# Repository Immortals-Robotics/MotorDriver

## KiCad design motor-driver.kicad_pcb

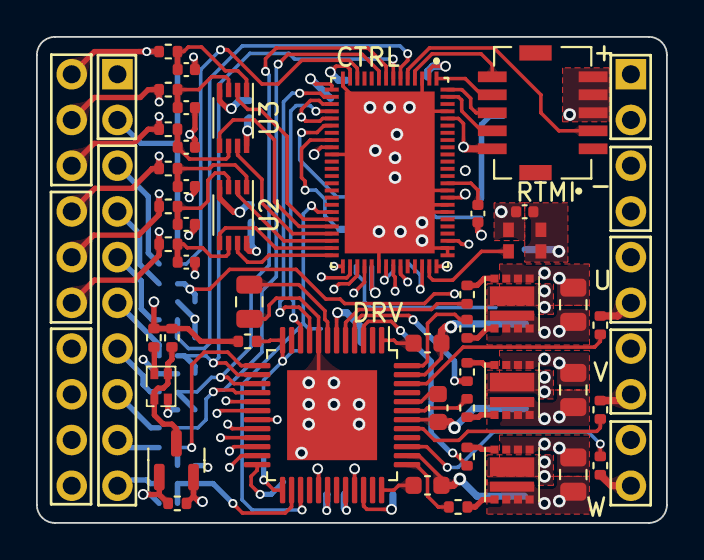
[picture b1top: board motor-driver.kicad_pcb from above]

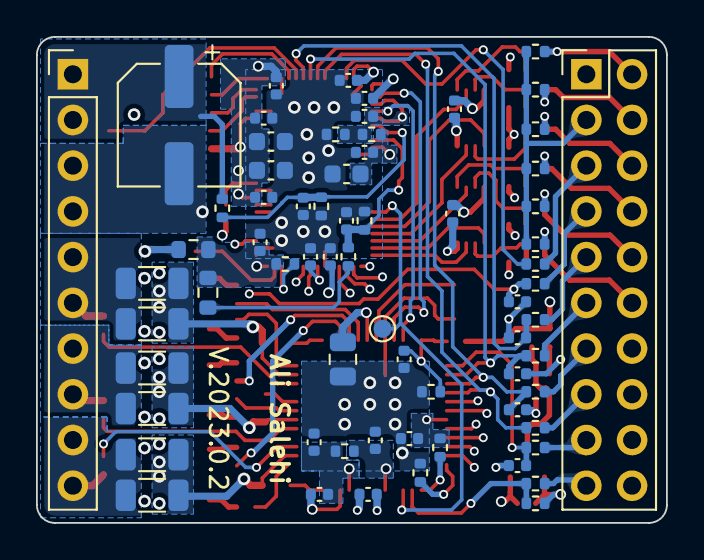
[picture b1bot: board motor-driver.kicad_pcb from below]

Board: 4 copper layers, 35.0 x 27.0 mm, 112 parts (67 on the bottom side), 98 nets.

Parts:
C1, C2, C3: 1nF; C_0402_1005Metric
C4, C5, C6, C41, C42, C43, C44, C45: 100pF; C_0402_1005Metric
C7, C8, C11, C12, C13, C14, C15, C16, C18, C19, C20, C21, C22, C23, C27, C28, C32, C33, C35, C36, C40: 100nF; C_0402_1005Metric
C9, C17: 4.7uF; C_0603_1608Metric
C10, C29, C30, C31: 470nF; C_0603_1608Metric
C24, C25, C37, C38, C39: 2.2uF; C_0805_2012Metric
C26: 22nF; C_0402_1005Metric
C34: 47uF; CP_Elec_6.3x7.7
D1: B2972USNB05
FB1: 600R, 1A; R_0603_1608Metric
J2: SIGNAL; PinHeader_2x10_P2.54mm_Vertical
J3: PWR; PinHeader_1x10_P2.54mm_Vertical
J4: RTMI; HRS_DF20EF-10DP-1V(52)
Q1: BSS138; SOT-23
Q4, Q5, Q6: SIZ342ADT; SIZ340DTT1GE3
R1, R2, R3, R4, R5, R6, R10, R11, R12, R15, R16, R20, R21, R22, R23: 4.7K; R_0402_1005Metric
R7, R8, R9, R19: 1K; R_0402_1005Metric
R13, R50: 10K; R_0402_1005Metric
R14, R17: 0; R_0402_1005Metric
R18: 47K; R_0402_1005Metric
R24, R27, R28, R29, R45: 270; R_0402_1005Metric
R25, R26, R46: 150; R_0402_1005Metric
R30, R31, R32, R33, R34, R35, R42, R43, R44: 10; R_0402_1005Metric
R36, R37, R38, R39, R40, R41: 0.005, 1W; R_1206_3216Metric
R47, R48: 330; R_0402_1005Metric
R49: 100; R_0402_1005Metric
R51: 1; R_0402_1005Metric
TH1: 10K; R_0603_1608Metric
TP1: EN TestPoint; TestPoint_Pad_D1.0mm
U1: TMC4671; QFN40P650X1050X90-77N
U2, U3: 74LVC3G17; VSSOP-8_2.3x2mm_P0.5mm
U4: TMC6200; TQFP-48-1EP_7x7mm_P0.5mm_EP5x5mm
XTAL1: MC2016, 25MHz; XTAL_MC2016K25_2X1P6_AVX

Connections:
+2V5: C36.2, R20.1, R21.2, U1.17 (ADC_I0_NEG), U1.19 (ADC_I1_NEG)
+3.3V: C7.2, C8.2, C9.2, C10.2, C11.2, C12.2, C13.2, C14.2, C15.2, C16.2, C33.2, FB1.1, J2.1, J4.1, R13.2, R17.1, TH1.1, U1.2 (VCCIO1), U1.13 (VCCIO2), U1.43 (VCCIO3), U1.52 (VCCIO4), U1.61 (VCCIO5), U1.72 (VCCIO6), U2.8 (VCC), U3.8 (VCC), U4.19 (VCC_IO)
+5V: C17.2, C18.2, J2.3, R4.2, R5.2, R6.2, R10.2, R11.2, R12.2, R15.2, R20.2, R47.2, R48.2, U1.23 (V5)
+24V: C23.2, C34.1, C37.2, C38.2, C39.2, J3.1, J3.2, Q4.2, Q4.3, Q4.4, Q4.10, Q5.2, Q5.3, Q5.4, Q5.10, Q6.2, Q6.3, Q6.4, Q6.10, R18.2, R51.1, U4.29 (VSA)
/CTRL_EN: C41.2, R24.1, U1.55 (ENI)
/CTRL_STATUS: R25.1, U1.12 (STATUS)
/CUR_U: U1.16 (ADC_I0_POS), U4.9 (CURU)
/CUR_V: U1.18 (ADC_I1_POS), U4.10 (CURV)
/Controller/ADC_VM: C35.2, R18.1, R19.2, U1.20 (ADC_VM)
/Controller/DRV_EN: TP1.1, U1.32 (ENO), U4.27 (DRV_EN)
/Controller/UH: U1.39 (PWM_UX1_H), U4.17 (UH)
/Controller/UL: U1.40 (PWM_UX1_L), U4.18 (UL)
/Controller/VH: U1.41 (PWM_VX2_H), U4.20 (VH)
/Controller/VL: U1.42 (PWM_VX2_L), U4.21 (VL)
/Controller/WH: U1.46 (PWM_WY1_H), U4.22 (WH)
/Controller/WL: U1.47 (PWM_WY1_L), U4.23 (WL)
/DBG_SPI_MISO: J4.9, U1.4 (GPIO6/AENC_VN_MCD/DBGSPI_MISO)
/DBG_SPI_MOSI: J4.7, U1.1 (GPIO5/AENC_UX_MCD/DBGSPI_MOSI)
/DBG_SPI_SCK: J4.5, U1.76 (GPIO4/AGPI_B_MCD/DBGSPI_SCK)
/DBG_SPI_TRG: J4.4, U1.5 (GPIO7/AENC_WY_MCD/DBGSPI_TRG)
/DRV_FAULT: R26.1, R49.2, U4.26 (FAULT)
/Driver/HSU: R30.1, U4.48 (HSU)
/Driver/HSV: R32.1, U4.43 (HSV)
/Driver/HSW: R34.1, U4.37 (HSW)
/Driver/LSU: R31.1, U4.5 (LSU)
/Driver/LSV: R33.1, U4.4 (LSV)
/Driver/LSW: R35.1, U4.3 (LSW)
/Driver/U_DRV: C29.1, Q4.9, R36.1, R37.1, U4.47 (U)
/Driver/U_SENSE: R42.1, U4.46 (USENSE)
/Driver/V_DRV: C30.1, Q5.9, R38.1, R39.1, U4.42 (V)
/Driver/V_SENSE: R43.1, U4.41 (VSENSE)
/Driver/W_DRV: C31.1, Q6.9, R40.1, R41.1, U4.38 (W)
/Driver/W_SENSE: R44.1, U4.39 (WSENSE)
/ENC_A: J2.2, R7.2, R10.1
/ENC_B: J2.4, R8.2, R11.1
/ENC_C: J2.6, R9.2, R12.1
/HALL_UX: J2.8, R1.2, R4.1
/HALL_V: J2.10, R2.2, R5.1
/HALL_WY: J2.12, R3.2, R6.1
/SPI_MISO: R46.1, U1.9 (SPI_MISO), U4.16 (SDO/SINGLE)
/SPI_MOSI: C45.2, R45.1, U1.8 (SPI_MOSI), U4.15 (SDI/AMPLX10)
/SPI_SCK: C44.2, R29.1, U1.7 (SPI_SCK), U4.14 (SCK/IDRV1)
/U: J3.5, J3.6, R36.2, R37.2, R42.2
/V: J3.7, J3.8, R38.2, R39.2, R43.2
/W: J3.9, J3.10, R40.2, R41.2, R44.2
/~CS_CTRL: C42.2, R27.1, U1.6 (SPI_~SCS)
/~CS_DBG_SPI: J4.3, U1.75 (GPIO3/AGPI_A_MCD/~DBGSPI_CS)
/~CS_DRV: C43.2, R28.1, U4.13 (~CS/IDRV0)
GND: C1.2, C2.2, C3.2, C4.2, C5.2, C6.2, C7.1, C8.1, C9.1, C10.1, C11.1, C12.1, C13.1, C14.1, C15.1, C16.1, C17.1, C18.1, C19.1, C20.1, C21.1, C22.1, C23.1, C24.1, C25.1, C28.1, C32.1, C33.1, C34.2, C35.1, C36.1, C37.1, C38.1, C39.1, C40.1, C41.1, C42.1, C43.1, C44.1, C45.1, D1.1 (K1), J2.14, J2.16, J2.18, J2.20, J3.3, J3.4, J4.6, J4.8, J4.10, Q1.2 (S), Q4.5, Q4.6, Q4.7, Q5.5, Q5.6, Q5.7, Q6.5, Q6.6, Q6.7, R14.1, R16.1, R19.1, R21.1, R23.1, R50.1, U1.3 (GNDIO1), U1.14 (GNDIO2), U1.24 (GNDA), U1.44 (GNDIO3), U1.53 (GNDIO4), U1.54 (TEST), U1.59 (PWM_IDLE_H), U1.60 (PWM_IDLE_L), U1.62 (GNDIO5), U1.73 (GNDIO6), U1.77 (EP), U2.4 (GND), U3.4 (GND), U4.8 (GNDA), U4.49 (EP), XTAL1.2 (GND)
unnamed: C1.1, R1.1, U2.1
unnamed: C2.1, R2.1, U2.3
unnamed: C3.1, R3.1, U2.6
unnamed: C4.1, R7.1, U3.1
unnamed: C5.1, R8.1, U3.3
unnamed: C6.1, R9.1, U3.6
unnamed: D1.2 (A1), D1.4 (K2), Q1.3 (D), R48.1
unnamed: D1.3 (A2), R47.1
unnamed: J2.5, R25.2
unnamed: J2.7, R24.2
unnamed: J2.9, R27.2
unnamed: J2.11, R29.2
unnamed: J2.13, R45.2
unnamed: J2.15, R46.2
unnamed: J2.17, R28.2
unnamed: J2.19, R26.2
unnamed: Q1.1 (G), R49.1, R50.2
unnamed: Q4.1, R30.2
unnamed: Q4.8, R31.2
unnamed: Q5.1, R32.2
unnamed: Q5.8, R33.2
unnamed: Q6.1, R34.2
unnamed: Q6.8, R35.2
unnamed: R22.2, TH1.2
unnamed: C40.2, R22.1, R23.2, U1.22 (AGPI_B)
unnamed: U1.51 (CLK), XTAL1.3 (OUT)
unnamed: U1.35 (ENC_A), U3.7
unnamed: U1.34 (ENC_B), U3.5
unnamed: U1.33 (ENC_N), U3.2
unnamed: U1.38 (HALL_UX), U2.7
unnamed: U1.37 (HALL_V), U2.5
unnamed: U1.36 (HALL_WY), U2.2
unnamed: C21.2, U1.15 (VCCCORE1)
unnamed: C20.2, U1.45 (VCCCORE2)
unnamed: C19.2, U1.63 (VCCCORE3)
unnamed: R13.1, U1.50 (~RST)
unnamed: C25.2, U4.7 (5VOUT)
unnamed: C24.2, U4.6 (12VOUT)
unnamed: R14.2, U4.24 (CLK)
unnamed: C26.2, U4.32 (CPI)
unnamed: C26.1, U4.30 (CPO)
unnamed: C29.2, U4.1 (CU)
unnamed: C30.2, U4.44 (CV)
unnamed: C31.2, U4.36 (CW)
unnamed: R17.2, U4.25 (SPE)
unnamed: C27.1, U4.34 (VCP)
unnamed: C32.2, R15.1, R16.2, U4.12 (VOFS/TEST)
unnamed: C27.2, C28.2, R51.2, U4.33 (VS)
unnamed: C22.2, FB1.2, XTAL1.1 (EN), XTAL1.4 (VCC)

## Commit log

2023-04-15 Add empty project and TMC4671
2023-04-15 Add TMC6200
2023-04-17 Added TMC4671 and TMC6200 and mosfets to the schematic.
2023-04-18 Finish controller and driver schematics.
2023-04-19 Remove the unused mosfets schematics file.
2023-04-19 Connected controller and driver sub-sheets.
2023-04-19 Add RTMI connector.
2023-04-20 Add stacking pin headers.
2023-04-21 Assign footprints and part numbers.
2023-04-22 Finish the initial placement, switch most of the parts to 0402.
2023-04-22 Add signal RCs and debug LEDs.
2023-04-23 Start routing.
2023-04-23 Finish draft routing,
2023-04-24 Improve routing.
2023-05-01 Reroute both main ICs to be able to adhere to the constraints.
2023-05-01 Add teardrops and organized the silkscreens.
2023-05-02 Generate greber files.
2023-05-02 Cleanup part properties.
2023-06-03 Fix issues found during the test, in the schematics.
2023-06-04 Applied the fixes to the pcb.
2023-06-04 Change the mosfets to SIZ342ADT.
2023-06-04 Small improvements.
2023-06-05 Minor adjustments to the PCB.
2023-06-09 Optimize the BOM.
